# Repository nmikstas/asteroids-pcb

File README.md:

# asteroids-pcb
PCB source for the original Asteroids arcade game. This is a reproduction of a rev. 2 PCB. There are two sets of gerber files: the main Asteroids PCB and a small adapter board for IC 8C. 8C was a masked ROM that is no longer available. The adapter PCB will allow a 2716 EPROM to be used in it's place. A 28C16A-25 flash ROM will also work.

# NOTE
This project is part of my project portfolio: https://nmikstas.github.io/portfolio/

# Folder Structure
* Asteroids_PCB - The Kicad design files for the Asteroids PCB
* ROM_to_2716 - The Kicad source files for the ROM to EPROM adapter PCB
* Gerbers_Asteroids - The gerber files for the Asteroids PCB
* Gerbers_ROM_to_EPROM - The gerber files for the ROM to EPROM adapter PCB
* BOM - Bill of materials for the Asteroids PCB

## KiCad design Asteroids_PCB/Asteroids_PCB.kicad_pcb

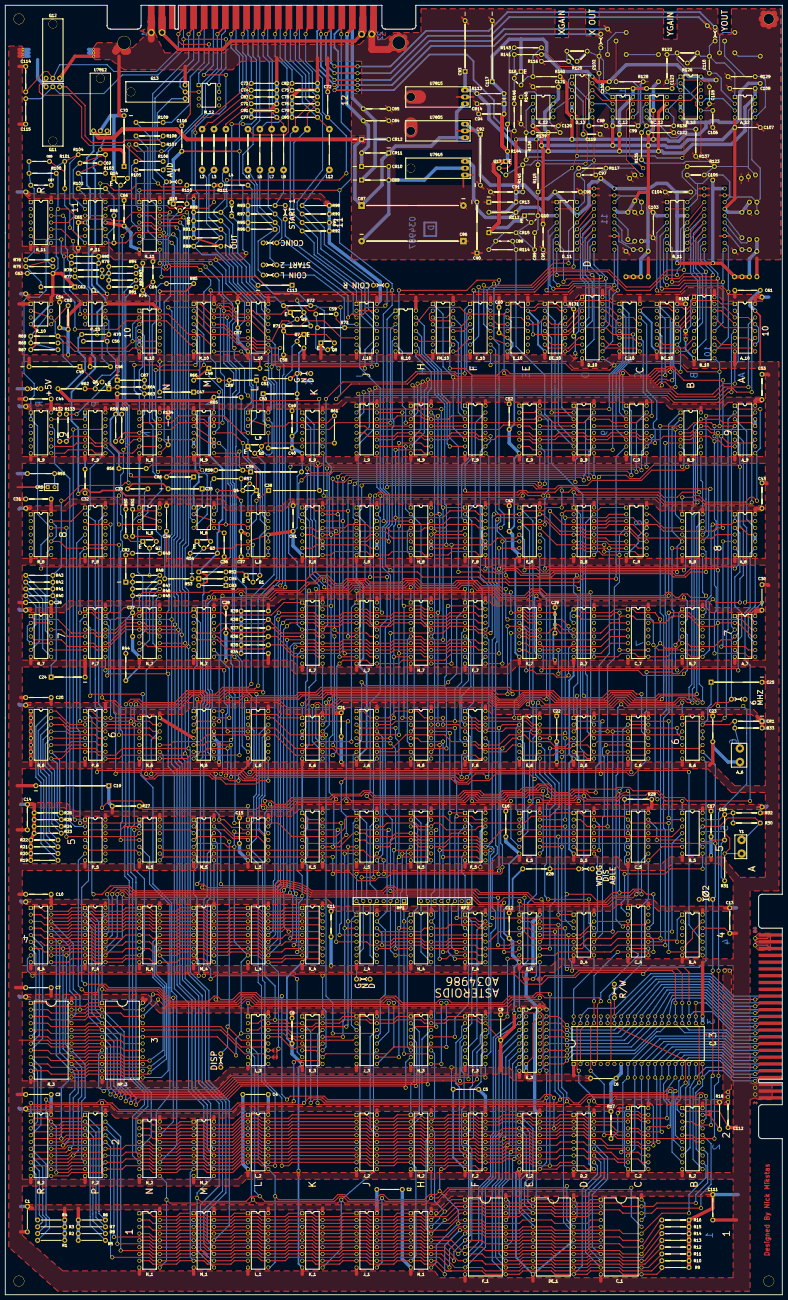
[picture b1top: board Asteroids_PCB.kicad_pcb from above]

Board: 2 copper layers, 290.8 x 482.6 mm, 490 parts (1 on the bottom side), 557 nets.

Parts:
A_6: RESET; RST
A_7: LS74; DIP14
A_8: LS10; DIP14
A_9: LS109; DIP16
A_10: LS157; DIP16
A_12: 082; DIP8
BC_10: LS157; DIP16
BC_12: 081; DIP8
B_2: LS244; DIP20
B_4: LS393; DIP14
B_5: LS04; DIP14
B_6: LS14; DIP14
B_7: LS161; DIP16
B_8: LS08; DIP14
B_9: LS32; DIP14
B_10: LS374; DIP20
B_11: AD561J; DIP16
B_11A1: ALT_DAC
B_12: 4016B; DIP14
C1, C2, C3, C4, C5, C6, C7, C8, C9, C10, C11, C12, C13, C14, C15, C16, C17, C18, C20, C21, C22, C23, C26, C28, C29, C30, C31, C34, C41, C42, C43, C44, C49, C52, C53, C57, C60, C61, C65, C66, C71, C72, C73, C74, C75, C76, C77, C78, C79, C80, C81, C82, C83, C84, C85, C91, C94, C111, C112: .1uF; GenericC
C19: 100uF; Electrolytic1
C24, C35, C47, C50, C62: 1uf; TantC
C25, C70, C90, C92, C93: 1uF; Electrolytic2C
C27, C32: .01uF; DiskC
C33: .22uF; Mylar_C
C36, C40, C55, C58: .01uf; DiskC
C37, C51, C54, C63, C95, C96, C99, C100, C103, C104, C107, C108, C114, C115, C116, C120, C121, C122, C123: .1uf; GenericC
C38, C39, C45, C48: 10uf; TantC2
C46: .047uf; Mylar_C
C56: .001uf; DiskC
C59: 270pf; Mylar_C
C64: .1uF; Mylar_C
C67, C68, C69: .1uf; Mylar_C
C86, C87: 470uF; Electrolytic3
C88: 390pf; SmallC
C89: 100pf; SmallC
C97, C105: 10pf; SmallC
C98, C106, C118, C119: 220pf; SmallC
C102, C110: 68pf; SmallC
C113: 1uF; TantC
C117: 22uF; Electrolytic4
CR1, CR2, CR3, CR4, CR6, CR7, CR8: 1N914; Diode1
CR5: LED
CR9, CR10, CR11, CR12: 1N4001; GenericD
CR13, CR14: 1N756A; GenericR
CR15: 1N914; GenericR
C_1: 8316E; DDIP24
C_2: LS244; DIP20
C_3: 6502A
C_4: 9316; DIP16
C_5, C_7: LS161; DIP16
C_6: LS00; DIP14
C_8: S287N; DIP16
C_9: LS191_; DIP16
C_10: LS157; DIP16
C_12: 082; DIP8
DE_1: 8316E; DDIP24
DE_10: LS157; DIP16
D_2: 2114; DIP18
D_4: LS74; DIP14
D_5: LS393; DIP14
D_6: LS02; DIP14
D_7: LS161; DIP16
D_8: LS174_; DIP16
D_9: LS191_; DIP16
D_10: LS374; DIP20
D_11: AD561J; DIP16
D_11A1: ALT_DAC
D_12: 4016B; DIP14
E_2: 2114; DIP18
E_3: LS245; DIP20
E_4: LS139; DIP16
E_5: LS20; DIP14
E_6: LS08; DIP14
E_7, E_8: LS42; DIP16
E_9: LS191_; DIP16
E_10: LS157; DIP16
E_12: 081; DIP8
FH_10: LS157; DIP16
F_1: 8316E; DDIP24
F_2: 82S137
F_3: LS157; DIP16
F_4: LS670; DIP16
F_5: LS193; DIP16
F_6: LS157_; DIP16
F_7: LS273; DIP20
F_8: SN5497; DIP16
F_9: LS191_; DIP16
F_10: LS174_; DIP16
H_1, H_2: 82S137
H_3: LS157; DIP16
H_4: LS670; DIP16
H_5: LS193; DIP16
H_6: LS367; DIP16
H_7: LS273; DIP20
H_8: SN5497; DIP16
H_9: LS191_; DIP16
H_10: LS04; DIP14
J20: J20
J21: J21
J_1, J_2: 82S137
J_3: LS157; DIP16
J_4: LS670; DIP16
J_5: LS193; DIP16
J_6: LS367; DIP16
J_7: LS273; DIP20
J_8: SN5497; DIP16
J_9: LS191_; DIP16
J_10: LS251; DIP16
K_1: 82S137
K_3: LS157; DIP16
K_4: 835185; DIP18
K_5: LS191; DIP16
K_6: LS08; DIP14
K_7: LS273; DIP20
K_8: SN5497; DIP16
K_9: LS164; DIP14
L2, L3, L4, L5, L6, L7, L8, L12: 100uH; GenericL
L_1, L_2: 82S137
L_3: LS139; DIP16
L_4: 835185; DIP18
L_5: LS04; DIP14
L_6: LS42; DIP16
L_8: 324; DIP14
L_9: 555; DIP8
L_10: LS251; DIP16
M_1, M_2: 82S137
M_4: 2114; DIP18
M_5: LS32; DIP14
M_6: LS83; DIP16
M_7: LS175; DIP16
M_8: 555; DIP8
M_9: 4016B; DIP14
M_10: LS259; DIP16
M_12: SW_DIP_x04; DIP8
NP_3: 8316E; DDIP24
N_1, N_2: 82S137
N_4: 2114; DIP18
N_5: LS00; DIP14
N_6: LS32; DIP14
N_7, N_11: LS174_; DIP16
N_8: 555; DIP8
N_9: LS06; DIP14
N_10: 4016B; DIP14
PD1, PD2, PD3, PD4, PD10, PD11, PD30, PD31: Split_Pad; SP
P_2: DIP20_DUMMY; DIP20
P_4: 2114; DIP18
P_5: LS86; DIP14
P_6: LS253; DIP16
P_7: LS174_; DIP16
P_8: LS161; DIP16
P_9: LS164; DIP14
P_10: 566; DIP8
P_11: 324; DIP14
Q1, Q2, Q3, Q4, Q5, Q7, Q10, Q16, Q17: 2N3906; GenericQ
Q6: 2N3643; GenericQ
Q8, Q9: 2N3904; GenericQ
Q11, Q12, Q13: 2N6044
Q14, Q15: MPSA06S; GenericQ
R1, R2, R3, R4, R5, R6, R7, R8, R45, R50: 22K; GenericR
R9, R10, R11, R12, R13, R14, R15, R16, R17, R18, R28, R33, R69, R110, R111, R130, R131: 10K; GenericR
R19, R20, R21, R22, R23, R24, R25, R26, R32, R87, R88, R89, R90, R91, R92, R93, R94, R95, R96, R97, R98, R99: 470; GenericR
R27, R29, R86: 1K; GenericR
R30, R31, R115: 330; GenericR
R34, R41: 22k; GenericR
R35, R100: 1.2k; GenericR
R36, R75, R117, R123, R133: 2.2k; GenericR
R37, R137, R140, R144: 4.7k; GenericR
R38, R54, R58, R59, R60, R63, R70, R79, R80, R103, R116, R122, R135, R136, R138, R139: 10k; GenericR
R39, R64, R106, R107, R108: 3.9k; GenericR
R40, R62, R67: 5.6k; GenericR
R42, R76, R114: 47k; GenericR
R43: 12k; GenericR
R44, R48, R78, R83: 47K; GenericR
R46, R81, R84, R143: 100K; GenericR
R47: 220K; GenericR
R49: 6.8K; GenericR
R51, R146: 18K; GenericR
R52: 33k; GenericR
R53, R73, R85, R132, R134: 1k; GenericR
R55: 150; GenericR
R56, R65: 3.3k; GenericR
R57, R61: 680; GenericR
R66: 2.7k; GenericC
R68: 15k; GenericR
R71: 68; GenericR
R72: 27; GenericR
R74, R142: 3.3K; GenericR
R77: 39K; GenericR
R82, R102: 4.7K; GenericR
R101: 270k; GenericR
R104, R128, R129: 6.8k; GenericR
R105, R109: 120; GenericR
R112, R113: 270; GenericR
R120, R126: 10k; Pot
R141: 2.2K; GenericR
R145: 56K; GenericR
RP1, RP2: R_Network07_10K; SIP8
R_2: LS245; DIP20
R_3: 8316E; DDIP24
R_4: 2114; DIP18
R_6: SW_x08; DIP16
R_7: LS08; DIP14
R_8: LS74; DIP14
R_9: LS164; DIP14
R_10: 555; DIP8
R_11: 4016B; DIP14
T1: TPAD1; TPAD
T2: TPAD2; TPAD
T3: TPAD3; TPAD
T4: TPAD4; TPAD
T5: TPAD5; TPAD
T6: TPAD6; TPAD
T7: TPAD7; TPAD
T10, T11, T12, T13, T14, T15, T16, T17: TPAD
TP1: WDOG_DISABLE; TEST_POINT
TP2: O2; TEST_POINT
TP3: R/W; TEST_POINT
TP4: 6MHz; TEST_POINT
TP5: +5V; TEST_POINT
TP6, TP7: GND; TEST_POINT
TP10: START 2; TEST_POINT
TP11: START 1; TEST_POINT
TP12: COIN R; TEST_POINT
TP13: COIN C; TEST_POINT
TP14: COIN L; TEST_POINT
TP20: AUD 1; TEST_POINT
TP30: DISP; TEST_POINT
TP50: X_OUT; TEST_POINT
TP60: Y_OUT; TEST_POINT
TP70: Z_OUT; TEST_POINT
U7805: L7805; Volt_Reg
U7812: L7812; 2N6044
U7815: L7815; Volt_Reg
U7915: L7915; Volt_Reg
Y1: 12.096MHz; RST

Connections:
1.5MHz: B_2.15, C_3.37, C_4.12
3KHz: B_4.8, C_5.2, D_5.1, L_10.3, R_11.11
3MHz: C_4.13, C_6.2, C_6.13, D_4.3, E_5.12, K_9.8
6MHz: A_7.3, A_9.4, B_10.11, C_4.14, D_10.11, F_10.9, TP4.1, TP4.2
12KHz: B_4.10, D_6.2, P_8.2, P_9.8, R_9.8
22V0: C37.1, C65.2, C87.1, CR11.1, CR12.1, L_8.4, P_11.4, U7805.1, U7812.1, U7815.1
36VAC1_: C84.1, CR10.1, CR11.2, J20.X
36_VAC2_: C85.1, CR9.1, CR12.2, J20.20
+5DAC: B_11.14, B_11A1.20, C92.1, C96.2, C104.2, D_11.14, D_11A1.20, U7805.3
+5V: A_7.14, A_8.14, A_9.16, A_10.16, BC_10.16, B_2.20, B_4.14, B_5.14, B_6.14, B_7.16, B_8.14, B_9.14, B_10.20, C1.1, C2.1, C3.1, C4.1, C5.1, C6.1, C7.1, C8.1, C9.1, C10.1, C11.1, C12.1, C13.1, C14.1, C15.1, C16.1, C17.1, C19.1, C20.1, C21.1, C22.1, C23.1, C26.1, C28.1, C29.1, C30.1, C31.1, C34.1, C41.1, C42.1, C43.1, C44.1, C49.1, C51.1, C52.1, C53.1, C54.1, C57.1, C60.1, C61.1, C62.1, C63.2, C66.1, C111.1, C112.1, CR1.1, C_1.21, C_1.24, C_2.20, C_3.8, C_4.16, C_5.16, C_6.14, C_7.16, C_8.16, C_9.16, C_10.16, DE_1.21, DE_1.24, DE_10.16, D_2.18, D_4.14, D_5.14, D_6.14, D_7.16, D_8.16, D_9.16, D_10.20, E_2.18, E_3.20, E_4.16, E_5.14, E_6.14, E_7.16, E_8.16, E_9.16, E_10.16, FH_10.16, F_1.21, F_1.24, F_2.18, F_3.16, F_4.16, F_5.16, F_6.16, F_7.20, F_8.16, F_9.16, F_10.16, H_1.18, H_2.18, H_3.16, H_4.16, H_5.16, H_6.16, H_7.20, H_8.16, H_9.16, H_10.14, J20.2, J20.21, J20.B, J20.Y, J21.45, J21.46, J21.47, J21.48, J21.49, J21.50, J_1.18, J_2.18, J_3.16, J_4.16, J_5.16, J_6.16, J_7.20, J_8.16, J_9.16, J_10.16, K_1.18, K_3.16, K_4.18, K_5.16, K_6.14, K_7.20, K_8.16, K_9.14, L_1.18, L_2.18, L_3.16, L_4.18, L_5.14, L_6.16, L_9.8, L_10.16, M_1.18, M_2.18, M_4.18, M_5.14, M_6.5, M_7.16, M_8.8, M_9.1, M_9.3, M_9.9, M_9.10, M_10.16, NP_3.21, NP_3.24, N_1.18, N_2.18, N_4.18, N_5.14, N_6.14, N_7.16, N_8.8, N_9.14, N_11.16, P_2.20, P_4.18, P_5.14, P_6.16, P_7.16, P_8.16, P_9.14, P_11.3, P_11.5, P_11.10, P_11.12, Q9.3, R1.1, R2.1, R3.1, R4.1, R5.2, R6.2, R7.2, R8.2, R9.2, R10.2, R11.1, R12.2, R13.1, R14.2, R15.1, R16.1, R17.1, R18.1, R19.1, R20.1, R21.1, R22.1, R23.1, R24.1, R25.1, R26.1, R27.2, R28.1, R29.2, R33.1, R39.1, R49.1, R50.1, R55.1, R67.1, R71.1, R79.1, R80.1, R87.2, R88.2, R89.2, R90.2, R91.2, R92.2, R93.2, R94.2, R95.2, R96.2, R97.2, R98.2, R99.2, R100.1, R130.2, R131.2, R132.2, R134.1, RP1.1, RP2.1, R_2.20, R_3.21, R_3.24, R_4.18, R_7.14, R_8.14, R_9.14, R_10.4, R_10.8, R_11.14, TP5.1, TP5.2
+8.2V: B_12.14, C94.1, C117.1, CR14.1, CR15.1, D_12.14, Q10.1, Q16.1, Q17.1, R113.1, R141.1, R144.1
+12V: C70.1, CR3.2, M_9.14, N_10.14, P_10.8, R52.1, R54.1, R56.1, R59.1, R60.1, R62.1, R63.1, R65.1, R70.1, R85.1, U7812.3
+15V: A_12.8, BC_12.7, C93.1, C100.2, C108.2, C121.2, C123.2, C_12.8, E_12.7, R113.2, U7815.3
-8.2V: B_12.7, C91.1, CR13.2, D_12.7, R112.1, R115.2, R142.2, R145.2
-15V: A_12.4, BC_12.4, B_11.3, B_11A1.17, C90.1, C95.1, C99.2, C103.1, C107.2, C120.2, C122.2, C_12.4, D_11.3, D_11A1.17, E_12.4, R112.2, U7915.3
A0: C_2.13, C_3.9, J21.17
A1: C_2.8, C_3.10, J21.18
A2: C_2.11, C_3.11, J21.15
A3: C_2.6, C_3.12, J21.16
A4: C_2.15, C_3.13, J21.13
A5: C_2.4, C_3.14, J21.14
A6: C_2.2, C_3.15, J21.11
A7: C_2.17, C_3.16, J21.12
A8: B_2.6, C_3.17, J21.9
A9: B_2.4, C_3.18, J21.10
A10: B_2.8, C_3.19, J21.7
A11: B_2.13, C_3.20, J21.8
A12: B_2.11, C_3.22, J21.21
A13: C_3.23, E_4.14, J21.22
A14: C_3.24, E_4.13, J21.19
A15: C_3.25, J21.20, PD1.1
AB0: C_1.8, C_2.7, DE_1.8, D_2.5, E_2.5, F_1.8, F_2.5, F_3.11, H_1.5, H_2.5, J_1.5, J_2.5, J_10.11, K_1.5, L_1.5, L_2.5, L_10.11, M_1.5, M_2.5, M_10.1, N_1.5, N_2.5, P_6.14
AB1: C_1.7, C_2.12, DE_1.7, D_2.6, E_2.6, F_1.7, F_2.6, F_3.5, H_1.6, H_2.6, J_1.6, J_2.6, J_10.10, K_1.6, L_1.6, L_2.6, L_10.10, M_1.6, M_2.6, M_10.2, N_1.6, N_2.6, P_6.2
AB2: C_1.6, C_2.9, DE_1.6, D_2.7, E_2.7, F_1.6, F_2.7, F_3.2, H_1.7, H_2.7, J_1.7, J_2.7, J_10.9, K_1.7, L_1.7, L_2.7, L_10.9, M_1.7, M_2.7, M_10.3, N_1.7, N_2.7
AB3: C_1.5, C_2.14, DE_1.5, D_2.4, E_2.4, F_1.5, F_2.4, F_3.14, H_1.4, H_2.4, J_1.4, J_2.4, K_1.4, L_1.4, L_2.4, M_1.4, M_2.4, N_1.4, N_2.4
AB4: C_1.4, C_2.5, DE_1.4, D_2.3, E_2.3, F_1.4, F_2.3, H_1.3, H_2.3, H_3.14, J_1.3, J_2.3, K_1.3, L_1.3, L_2.3, M_1.3, M_2.3, N_1.3, N_2.3
AB5: C_1.3, C_2.16, DE_1.3, D_2.2, E_2.2, F_1.3, F_2.2, H_1.2, H_2.2, H_3.2, J_1.2, J_2.2, K_1.2, L_1.2, L_2.2, M_1.2, M_2.2, N_1.2, N_2.2
AB6: C_1.2, C_2.18, DE_1.2, D_2.1, E_2.1, F_1.2, F_2.1, H_1.1, H_2.1, H_3.5, J_1.1, J_2.1, K_1.1, L_1.1, L_2.1, M_1.1, M_2.1, N_1.1, N_2.1
AB7: C_1.1, C_2.3, DE_1.1, D_2.17, E_2.17, F_1.1, F_2.17, H_1.17, H_2.17, H_3.11, J_1.17, J_2.17, K_1.17, L_1.17, L_2.17, M_1.17, M_2.17, N_1.17, N_2.17
AB8: B_2.14, C_1.23, DE_1.23, F_1.23, F_2.16, H_1.16, H_2.16, J_1.16, J_2.16, J_3.11, K_1.16, L_1.16, L_2.16, M_1.16, M_2.16, N_1.16, N_2.16, P_5.4
AB9: B_2.16, C_1.22, DE_1.22, D_2.15, E_2.15, F_1.22, F_2.15, H_1.15, H_2.15, J_1.15, J_2.15, J_3.14, K_1.15, L_1.15, L_2.15, L_6.15, M_1.15, M_2.15, N_1.15, N_2.15, N_5.5
AB10: B_2.12, C_1.19, DE_1.19, E_4.2, F_1.19, F_2.8, H_1.8, H_2.8, J_1.8, J_2.8, J_3.2, K_1.8, L_5.5, L_6.14
AB11: B_2.7, E_4.3, K_3.2, L_3.2, L_6.13
AB12: B_2.9, D_6.8, E_5.9, K_3.14, L_3.3
ADMA0: C_8.5, D_8.12, E_8.15, F_3.10
ADMA1: F_3.6, F_4.15, F_5.3
ADMA2: F_3.3, F_4.1, F_5.2
ADMA3: F_3.13, F_4.2, F_5.6
ADMA4: F_4.3, F_5.7, H_3.13
ADMA5: H_3.3, H_4.15, H_5.3
ADMA6: H_3.6, H_4.1, H_5.2
ADMA7: H_3.10, H_4.2, H_5.6
ADMA8: H_4.3, H_5.7, J_3.10
ADMA9: J_3.13, J_4.15, J_5.3
ADMA10: J_3.3, J_4.1, J_5.2
ADMA11: J_4.2, J_5.6, K_3.3
ADMA12: J_4.3, J_5.7, K_3.13
AM0: F_3.9, K_4.5, L_4.5, M_4.5, NP_3.8, N_4.5, P_4.5, R_3.8, R_4.5
AM1: F_3.7, K_4.6, L_4.6, M_4.6, NP_3.7, N_4.6, P_4.6, R_3.7, R_4.6
AM2: F_3.4, K_4.7, L_4.7, M_4.7, NP_3.6, N_4.7, P_4.7, R_3.6, R_4.7
AM3: F_3.12, K_4.4, L_4.4, M_4.4, NP_3.5, N_4.4, P_4.4, R_3.5, R_4.4
AM4: H_3.12, K_4.3, L_4.3, M_4.3, NP_3.4, N_4.3, P_4.3, R_3.4, R_4.3
AM5: H_3.4, K_4.2, L_4.2, M_4.2, NP_3.3, N_4.2, P_4.2, R_3.3, R_4.2
AM6: H_3.7, K_4.1, L_4.1, M_4.1, NP_3.2, N_4.1, P_4.1, R_3.2, R_4.1
AM7: H_3.9, K_4.17, L_4.17, M_4.17, NP_3.1, N_4.17, P_4.17, R_3.1, R_4.17
AM8: J_3.9, K_4.16, L_4.16, M_4.16, NP_3.23, N_4.16, P_4.16, R_3.23, R_4.16
AM9: J_3.12, K_4.15, L_4.15, M_4.15, NP_3.22, N_4.15, P_4.15, R_3.22, R_4.15
AM10: J_3.4, K_4.8, L_4.8, L_5.3, M_5.5, NP_3.19, R_3.19
AM11: K_3.4, L_3.14
AM12: K_3.12, L_3.13
AUDIO_1_: C113.2, J20.5, P_11.8, R86.1, TP20.1, TP20.2
AUDIO_2_: J20.E, P_11.14, R110.1
BVLD: B_8.8, K_9.2
C1: C115.1, J20.4, M_12.7, M_12.8, Q11.2
C_CN_SW_: C81.2, J20.12, L7.1
D0: C_3.33, E_3.18, J21.29
D1: C_3.32, E_3.17, J21.30
D2: C_3.31, E_3.16, J21.27
D3: C_3.30, E_3.15, J21.28
D4: C_3.29, E_3.14, J21.25
D5: C_3.28, E_3.13, J21.26
D6: C_3.27, E_3.12, J21.23
D7: C_3.26, E_3.11, J21.24
DACX1: C_10.9, D_10.13
DACX1*: D_10.12, D_11.4, D_11A1.12
DACX2: C_10.7, D_10.14
DACX2*: D_10.15, D_11.5, D_11A1.11
DACX3: C_10.12, D_10.17
DACX3*: D_10.16, D_11.6, D_11A1.10
DACX4: C_10.4, D_10.18
DACX4*: D_10.19, D_11.7, D_11A1.9
DACX5: DE_10.9, D_10.8
DACX5*: D_10.9, D_11.8, D_11A1.8
DACX6: DE_10.7, D_10.7
DACX6*: D_10.6, D_11.9, D_11A1.7
DACX7: DE_10.12, D_10.4
DACX7*: D_10.5, D_11.10, D_11A1.6
DACX8: DE_10.4, D_10.3
DACX8*: D_10.2, D_11.11, D_11A1.5
DACX9: E_10.12, F_10.13
DACX9*: D_11.12, D_11A1.4, F_10.12
DACX10: E_10.4, F_10.14
DACX10*: D_11.13, D_11A1.3, F_10.15
DACY1: A_10.9, B_10.13
DACY1*: B_10.12, B_11.4, B_11A1.12
DACY2: A_10.7, B_10.14
DACY2*: B_10.15, B_11.5, B_11A1.11
DACY3: A_10.12, B_10.17
DACY3*: B_10.16, B_11.6, B_11A1.10
DACY4: A_10.4, B_10.18
DACY4*: B_10.19, B_11.7, B_11A1.9
DACY5: BC_10.9, B_10.8
DACY5*: B_10.9, B_11.8, B_11A1.8
DACY6: BC_10.7, B_10.7
DACY6*: B_10.6, B_11.9, B_11A1.7
DACY7: BC_10.12, B_10.4
DACY7*: B_10.5, B_11.10, B_11A1.6
DACY8: BC_10.4, B_10.3
DACY8*: B_10.2, B_11.11, B_11A1.5
DACY9: FH_10.9, F_10.6
DACY9*: B_11.12, B_11A1.4, F_10.7
DACY10: FH_10.12, F_10.4
DACY10*: B_11.13, B_11A1.3, F_10.5
DB0: C_1.9, DE_1.9, D_2.14, E_3.2, F_1.9, H_1.14, J_1.14, K_1.14, L_1.14, M_1.14, N_1.14, N_7.6, N_11.14, P_2.17, P_6.7, R14.1, R_2.16
DB1: C_1.10, DE_1.10, D_2.13, E_3.3, F_1.10, H_1.13, J_1.13, K_1.13, L_1.13, M_1.13, N_1.13, N_7.11, N_11.3, P_2.18, P_6.9, R12.1, R_2.17
DB2: C_1.11, DE_1.11, D_2.12, E_3.4, F_1.11, H_1.12, J_1.12, K_1.12, L_1.12, M_1.12, N_1.12, N_7.4, N_11.13, P_2.19, P_7.6, R10.1, R_2.18
DB3: C_1.13, DE_1.13, D_2.11, E_3.5, F_1.13, H_1.11, J_1.11, K_1.11, L_1.11, M_1.11, N_1.11, N_7.13, N_11.4, P_2.16, P_7.11, R9.1, R_2.15
DB4: C_1.14, DE_1.14, E_2.14, E_3.6, F_1.14, F_2.14, H_2.14, J_2.14, L_2.14, M_2.14, N_2.14, N_7.3, N_11.11, P_2.15, P_7.4, R11.2, R_2.14
DB5: C_1.15, DE_1.15, E_2.13, E_3.7, F_1.15, F_2.13, H_2.13, J_2.13, L_2.13, M_2.13, N_2.13, N_11.6, P_2.14, P_7.13, R13.2, R_2.13
DB6: C_1.16, DE_1.16, E_2.12, E_3.8, F_1.16, F_2.12, H_2.12, J_2.12, L_2.12, M_2.12, N_2.12, P_2.13, P_7.3, R15.2, R_2.12
DB7: C_1.17, DE_1.17, E_2.11, E_3.9, F_1.17, F_2.11, H_2.11, J_2.11, J_10.6, L_2.11, L_10.6, M_2.11, M_10.13, N_2.11, P_2.12, P_7.14, R16.2, R_2.11
DDMA0: F_7.18, H_7.18, J_7.18, K_7.18, L_4.14, M_4.14, NP_3.9, N_4.14, P_2.3, R8.1, R_2.4, R_3.9
DDMA1: F_7.3, H_7.3, J_7.3, K_7.3, L_4.13, M_4.13, NP_3.10, N_4.13, P_2.2, R7.1, R_2.3, R_3.10
DDMA2: F_7.17, H_7.17, J_7.17, K_7.17, L_4.12, M_4.12, NP_3.11, N_4.12, P_2.1, R6.1, R_2.2, R_3.11
DDMA3: F_7.4, H_7.4, J_7.4, K_7.4, L_4.11, M_4.11, NP_3.13, N_4.11, P_2.4, R5.1, R_2.5, R_3.13
DDMA4: F_7.14, H_7.14, J_7.14, K_4.14, K_7.14, NP_3.14, P_2.5, P_4.14, R1.2, R_2.6, R_3.14, R_4.14
DDMA5: F_7.7, H_7.7, J_7.7, K_4.13, K_7.7, NP_3.15, P_2.6, P_4.13, R2.2, R_2.7, R_3.15, R_4.13
DDMA6: F_7.13, H_7.13, J_7.13, K_4.12, K_7.13, NP_3.16, P_2.7, P_4.12, R3.2, R_2.8, R_3.16, R_4.12
DDMA7: F_7.8, H_7.8, J_7.8, K_4.11, K_7.8, NP_3.17, P_2.8, P_4.11, R4.2, R_2.9, R_3.17, R_4.11
DIAG_STEP_: C71.2, J20.K, L4.1
DVX0: E_9.15, J_7.19, J_8.14
DVX1: E_9.1, J_7.2, J_8.15
DVX2: E_9.10, J_7.16, J_8.2
DVX3: E_9.9, J_7.5, J_8.3
DVX4: D_9.15, J_7.15, K_8.4
DVX5: D_9.1, J_7.6, K_8.1
DVX6: D_9.10, J_7.12, K_8.14
DVX7: D_9.9, J_7.9, K_8.15
DVX8: C_9.15, K_7.19, K_8.2
DVX9: C_9.1, K_7.2, K_8.3
DVX10: C_9.5, C_9.10, D_9.5, E_9.5, K_7.16
DVX11: B_6.3, C_9.9, F_6.11, K_7.5
DVY0: H_6.2, H_7.19, H_8.14, J_9.15
DVY1: H_6.14, H_7.2, H_8.15, J_9.1
DVY2: H_6.12, H_7.16, H_8.2, J_9.10
DVY3: H_6.4, H_7.5, H_8.3, J_9.9
DVY4: F_8.4, H_6.10, H_7.15, H_9.15
DVY5: F_8.1, H_6.6, H_7.6, H_9.1
DVY6: F_8.14, H_7.12, H_9.10, J_6.4
DVY7: F_8.15, H_7.9, H_9.9, J_6.2
DVY8: F_7.19, F_8.2, F_9.15, J_6.10
DVY9: F_7.2, F_8.3, F_9.1, J_6.6
DVY10: F_7.16, F_9.5, F_9.10, H_9.5, J_6.12, J_9.5
DVY11: F_6.14, F_7.5, F_9.9, J_6.14
EXPAUD0: P_7.12, R_7.1
EXPAUD1: P_7.5, R_7.12
EXPAUD2: P_7.10, R_7.4
EXPAUD3: P_7.7, R_7.9
EXPITCH0: L_5.11, N_6.12, P_7.2, P_8.4
EXPITCH1: N_6.13, P_7.15, P_8.3
EXPLOSND: C24.2, R40.1, R41.1, R42.1, R43.1, R82.2
FIRE_: C72.2, J20.T, L_10.15, R89.1
GND: A_6.1, A_7.7, A_8.7, A_9.8, A_10.8, A_10.15, BC_10.8, BC_10.15, B_2.1, B_2.10, B_2.19, B_4.2, B_4.7, B_4.12, B_5.7, B_6.7, B_7.8, B_8.7, B_9.7, B_10.1, B_10.10, B_11.1, B_11A1.1, B_11A1.2, B_11A1.13, B_11A1.19, C1.2, C2.2, C3.2, C4.2, C5.2, C6.2, C7.2, C8.2, C9.2, C10.2, C11.2, C12.2, C13.2, C14.2, C15.2, C16.2, C17.2, C19.2, C20.2, C21.2, C22.2, C23.2, C24.1, C25.2, C26.2, C27.2, C28.2, C29.2, C30.2, C31.2, C32.2, C33.2, C34.2, C35.2, C36.2, C37.2, C38.2, C39.1, C40.2, C41.2, C42.2, C43.2, C44.2, C45.2, C46.2, C47.2, C48.1, C49.2, C50.2, C51.2, C52.2, C53.2, C54.2, C55.2, C57.2, C58.2, C60.2, C61.2, C63.1, C64.2, C65.1, C66.2, C70.2, C71.1, C72.1, C73.1, C74.1, C75.1, C76.1, C77.1, C78.1, C79.1, C80.1, C81.1, C82.1, C83.1, C84.2, C85.2, C86.2, C87.2, C90.2, C91.2, C92.2, C93.2, C94.2, C95.2, C96.1, C98.2, C99.1, C100.1, C103.2, C104.1, C106.2, C107.1, C108.1, C111.2, C112.2, C114.2, C115.2, C116.2, C117.2, C118.2, C119.2, C120.1, C121.1, C122.1, C123.1, CR5.1, CR7.1, CR13.1, CR14.2, C_1.12, C_1.18, C_2.1, C_2.10, C_2.19, C_3.1, C_3.21, C_4.8, C_5.3, C_5.4, C_5.6, C_5.8, C_6.7, C_7.8, C_8.8, C_8.13, C_8.14, C_9.8, C_10.8, C_10.15, DE_1.12, DE_1.18, DE_10.8, DE_10.15, D_2.9, D_4.7, D_5.7, D_6.7, D_7.8, D_8.8, D_9.8, D_10.1, D_10.10, D_11.1, D_11A1.1, D_11A1.2, D_11A1.13, D_11A1.19, E_2.9, E_3.10, E_3.19, E_4.8, E_4.15, E_5.7, E_6.7, E_7.8, E_8.8, E_9.8, E_10.6, E_10.8, E_10.15, FH_10.3, FH_10.8, FH_10.15, F_1.12, F_1.18, F_2.9, F_3.8, F_3.15, F_4.8, F_5.8, F_5.14, F_6.5, F_6.8, F_6.15, F_7.10, F_8.8, F_9.8, F_10.8, H_1.9, H_2.9, H_3.8, H_3.15, H_4.8, H_5.8, H_5.14, H_6.8, H_7.10, H_8.1, H_8.4, H_8.8, H_9.8, H_10.7, J20.1, J20.11, J20.22, J20.A, J20.U, J20.V, J20.Z, J21.1, J21.2, J21.3, J21.4, J21.5, J21.6, J_1.9, J_2.9, J_3.8, J_3.15, J_4.8, J_5.8, J_5.14, J_6.8, J_7.10, J_8.1, J_8.4, J_8.8, J_9.8, J_10.8, K_1.9, K_3.8, K_3.15, K_4.9, K_5.1, K_5.4, K_5.8, K_5.9, K_5.10, K_5.15, K_6.7, K_7.10, K_8.8, K_9.7, L_1.9, L_2.9, L_3.8, L_3.15, L_4.9, L_5.7, L_6.8, L_8.5, L_8.10, L_8.11, L_9.1, L_10.8, M_1.9, M_2.9, M_4.9, M_5.7, M_6.12, M_6.13, M_7.8, M_8.1, M_9.7, M_10.8, NP_3.12, NP_3.18, N_1.9, N_2.9, N_4.9, N_5.7, N_6.7, N_7.8, N_8.1, N_9.7, N_10.1, N_10.3, N_10.7, N_11.8, PD1.2, PD2.1, PD2.2, PD3.1, PD3.2, PD4.1, PD4.2, PD30.1, PD30.2, PD31.1, PD31.2, P_2.10, P_4.9, P_5.7, P_6.8, P_7.8, P_8.8, P_9.7, P_10.1, P_11.11, Q7.3, Q8.1, Q11.3, Q12.3, Q13.3, Q14.1, Q15.1, R17.2, R18.2, R32.2, R34.2, R44.2, R53.2, R72.2, R116.2, R122.2, R128.2, R129.2, R130.1, R131.1, R137.2, R140.2, R_2.10, R_3.12, R_3.18, R_4.9, R_6.1, R_6.2, R_6.3, R_6.4, R_6.5, R_6.6, R_6.7, R_6.8, R_7.7, R_8.7, R_9.7, R_10.1, R_11.7, TP6.1, TP6.2, TP7.1, TP7.2, U7805.2, U7812.2, U7815.2, U7915.1
GO: A_9.6, B_7.9, C_7.9, D_7.7, D_7.9, D_7.10, H_10.1
GR: B_5.4, F_4.11, H_4.11, J_4.11
GW: C_6.3, F_4.12, H_4.12, J_4.12
HALT: A_9.10, D_8.14, L_10.2
HYPRSPC_: C73.2, J20.10, L_10.1, R88.1
INV: B_12.13, D_12.13, Q16.3, R142.1, R143.2
L1: C114.1, J20.D, M_12.1, Q12.2
LIFEEN: M_10.10, R79.2, R_11.12
LIFESND: R78.2, R_11.10
LOAD1: F_4.10, F_5.15, H_6.3, RP2.3
LOAD2: F_4.9, F_5.1, H_6.13, RP2.4
LOAD3: F_4.7, F_5.10, H_6.11, RP2.6
LOAD4: F_4.6, F_5.9, H_6.5, RP2.5
LOAD5: H_4.10, H_5.15, H_6.9, RP2.7
LOAD6: H_4.9, H_5.1, H_6.7, RP2.8
LOAD7: H_4.7, H_5.10, J_6.5, RP1.3
LOAD8: H_4.6, H_5.9, J_6.3, RP1.2
LOAD9: J_4.10, J_5.15, J_6.9, RP1.5
LOAD10: J_4.9, J_5.1, J_6.7, RP1.6
LOAD11: J_4.7, J_5.10, J_6.11, RP1.7
LOAD12: J_4.6, J_5.9, J_6.13, RP1.8
L_CN_SW_: C82.2, J20.13, L5.1
NINV: B_12.12, D_12.12, Q17.3, R145.1
NOISE: N_5.3, R_8.12, R_9.1, R_9.2, R_11.9
NO_CON: J20.19, R146.2
unnamed: A_6.2, B_6.13, C25.1, CR1.2, R33.2
unnamed: A_7.5, A_8.3, A_8.10, A_8.11
unnamed: A_7.8, B_9.5
unnamed: A_7.9, A_8.5
unnamed: A_7.10, A_8.8
unnamed: A_8.1, A_8.2, A_8.13, B_7.15
unnamed: A_8.4, C_8.4, D_6.12, D_8.7
unnamed: A_8.6, E_8.12
unnamed: A_8.9, L_5.12
unnamed: A_9.2, B_6.2
unnamed: A_9.15, B_8.11
unnamed: A_12.2, C110.1, R122.1, R126.3
unnamed: A_12.3, B_12.2, B_12.10
unnamed: A_12.5, R129.1
unnamed: A_12.7, B_12.8, C105.1, R123.1, R135.2
unnamed: BC_12.2, R135.1, R136.2
unnamed: BC_12.3, R137.1
unnamed: BC_12.6, B_12.4, R136.1
unnamed: B_4.1, C_4.11
unnamed: B_4.6, B_4.13
unnamed: B_5.2, C_6.1
unnamed: B_5.5, C_5.15
unnamed: B_5.6, C_3.6, C_5.9
unnamed: B_5.8, C_4.2
unnamed: B_5.10, C18.1, R31.1
unnamed: B_5.11, R31.2, Y1.2
unnamed: B_5.9, B_5.12, R30.2, Y1.1
unnamed: B_5.13, C18.2, R30.1, R32.1
unnamed: B_6.4, F_6.2
unnamed: B_6.10, C_6.5, D_4.10
unnamed: B_6.11, B_6.12
unnamed: B_7.3, E_7.9
unnamed: B_7.4, E_7.10
unnamed: B_7.5, E_7.11
unnamed: B_7.7, B_7.10, C_7.15
unnamed: B_8.3, C_8.15
unnamed: B_8.6, F_5.5
unnamed: B_9.3, K_6.12
unnamed: B_9.6, D_8.9
unnamed: B_9.8, K_6.9
unnamed: B_9.10, D_4.6
unnamed: B_11.16, R123.2
unnamed: B_11A1.14, T7.1
unnamed: B_11A1.15, T6.1
unnamed: B_11A1.16, T5.1
unnamed: B_12.1, B_12.3, C118.1
unnamed: B_12.9, B_12.11, C106.1
unnamed: C27.1, CR2.1, Q2.2, R44.1, R45.1, R46.1, R47.1, R48.1
unnamed: C32.1, N_8.5
unnamed: C33.1, N_8.2, N_8.6, Q2.3, R51.2
unnamed: C35.1, M_8.2, M_8.6, R57.2
unnamed: C36.1, M_8.5
unnamed: C38.1, L_8.3, M_9.4, Q3.3
unnamed: C39.2, M_9.8, R58.1
unnamed: C40.1, L_9.5
unnamed: C45.1, N_10.2, N_10.9, Q6.2, R69.2, R_10.2, R_10.6
unnamed: C46.1, P_10.7
unnamed: C47.1, L_8.12, M_9.11, Q1.3
unnamed: C48.2, M_9.2, R66.1
unnamed: C50.1, L_9.2, L_9.6, R61.2
unnamed: C55.1, R_10.5
unnamed: C56.1, P_10.6, R70.2
unnamed: C56.2, P_10.5, Q6.3, R62.2
unnamed: C58.1, Q7.1, Q8.3, Q9.2, R71.2
unnamed: C59.1, Q8.2, R73.1
unnamed: C59.2, H_10.4, R73.2
unnamed: C62.2, R75.1, R76.2
unnamed: C64.1, N_8.3, R74.1
unnamed: C67.1, P_11.7, R101.1, R104.2
unnamed: C67.2, C68.1, R76.1, R100.2
unnamed: C68.2, P_11.6, R101.2
unnamed: C69.2, P_11.2, R103.2, R104.1
unnamed: C86.1, CR9.2, CR10.2, U7915.2
unnamed: C88.1, C89.1, CR15.2, Q10.2, R114.1
unnamed: C88.2, C_6.11, R114.2
unnamed: C97.1, C_12.7, D_12.8, R117.1, R138.2
unnamed: C97.2, C_12.6, D_11.2, D_11.15
unnamed: C98.1, D_12.9, D_12.11
unnamed: C102.1, C_12.2, R116.1, R120.3
unnamed: C113.1, R111.2
unnamed: C119.1, D_12.1, D_12.3
unnamed: CR2.2, R49.2
unnamed: CR3.1, CR4.2
unnamed: CR4.1, Q1.2, Q3.2, R53.1
unnamed: CR5.2, R55.2
unnamed: CR6.1, M_8.3
unnamed: CR7.2, N_10.4, R64.1
unnamed: CR8.1, L_9.3
unnamed: C_6.6, D_5.2, D_5.12
unnamed: C_6.8, E_4.1
unnamed: C_6.10, D_6.10
unnamed: C_7.3, E_7.4
unnamed: C_7.4, E_7.5
unnamed: C_7.5, E_7.6
unnamed: C_7.6, E_7.7
unnamed: C_7.7, C_7.10, D_7.15
unnamed: C_8.1, E_6.6
unnamed: C_8.2, E_6.3
unnamed: C_8.3, E_6.11
unnamed: C_8.6, D_8.5, E_8.14
unnamed: C_8.7, D_8.10, E_8.13, L_5.13
unnamed: C_8.9, D_8.6
unnamed: C_8.10, D_8.11
unnamed: C_8.11, D_8.4
unnamed: C_8.12, D_8.13
unnamed: C_9.4, D_9.13
unnamed: C_9.7, H_10.13
unnamed: C_9.14, D_9.14, E_9.14, H_10.6
unnamed: C_12.3, D_12.2, D_12.10
unnamed: C_12.5, R128.1
unnamed: D_2.8, E_2.8, M_5.11
unnamed: D_2.16, E_2.16, P_5.6
unnamed: D_4.11, D_5.8
unnamed: D_4.12, E_6.8
unnamed: D_5.6, D_5.13
unnamed: D_6.1, R_8.11
unnamed: D_6.3, L_5.2, P_8.9
unnamed: D_6.4, E_5.13
unnamed: D_6.5, D_6.9, E_4.11
unnamed: D_6.11, D_8.15
unnamed: D_7.4, E_7.1
unnamed: D_7.5, E_7.2
unnamed: D_7.6, E_7.3
unnamed: D_9.4, E_9.13
unnamed: D_11.16, R117.2
unnamed: D_11A1.14, T4.1
unnamed: D_11A1.15, T3.1
unnamed: D_11A1.16, T2.1
unnamed: D_11A1.18, T1.1
unnamed: D_12.4, E_12.6, R139.1
unnamed: E_5.8, L_6.12
unnamed: E_6.10, R28.2, TP1.1, TP1.2
unnamed: E_7.12, M_6.15
unnamed: E_7.13, M_6.2
unnamed: E_7.14, M_6.6
unnamed: E_7.15, M_6.9
unnamed: E_12.2, R138.1, R139.2
unnamed: E_12.3, R140.1
unnamed: F_5.12, H_5.5
unnamed: F_6.4, M_6.7
unnamed: F_6.7, M_6.16
unnamed: F_6.9, M_6.4
unnamed: F_6.12, M_6.11
unnamed: F_7.1, K_6.3, K_6.4
unnamed: F_8.5, H_8.12
unnamed: F_8.7, H_8.10, H_8.11
unnamed: F_9.4, H_9.13
unnamed: F_9.7, H_10.11
unnamed: F_9.14, H_9.14, H_10.8, J_9.14
unnamed: H_5.12, J_5.5
unnamed: H_7.1, K_6.6
unnamed: H_9.4, J_9.13
unnamed: H_10.3, K_9.3
unnamed: H_10.5, J_8.6
unnamed: H_8.6, H_10.9
unnamed: J_8.10, J_8.11, K_8.7
unnamed: J_8.12, K_8.5
unnamed: J_10.1, L8.2, R93.1, TP11.1, TP11.2
unnamed: J_10.2, L12.2, R98.1, TP12.1, TP12.2
unnamed: J_10.3, L7.2, R97.1, TP13.1, TP13.2
unnamed: J_10.4, L5.2, R96.1, TP14.1, TP14.2
unnamed: J_10.15, L6.2, R95.1, TP10.1, TP10.2
unnamed: K_3.7, M_5.9
unnamed: K_5.14, K_6.8
unnamed: K_6.11, K_7.11
unnamed: L3.2, L_10.13, R91.1
unnamed: L4.2, L_10.14, R90.1
unnamed: L_1.8, L_2.8, L_5.6, M_1.8, M_2.8, N_1.8, N_2.8
unnamed: L_5.1, P_8.15
unnamed: L_5.4, M_5.2
unnamed: L_5.10, P_8.5
unnamed: L_8.1, Q4.2
unnamed: L_8.2, Q4.1, R56.2
unnamed: L_8.6, L_8.7
unnamed: L_8.8, L_8.9
unnamed: L_8.13, Q5.1, R65.2
unnamed: L_8.14, Q5.2
unnamed: L_9.7, Q5.3, R61.1
unnamed: M_4.8, M_5.6, R_4.8
unnamed: M_5.3, N_4.8, P_4.8
unnamed: M_6.1, M_7.7
unnamed: M_6.3, M_7.10
unnamed: M_6.8, M_7.2
unnamed: M_6.10, M_7.15
unnamed: M_7.9, N_6.8
unnamed: M_8.7, Q4.3, R57.1
unnamed: M_9.5, M_9.6, N_9.10, R60.2
unnamed: M_9.12, M_9.13, N_9.4, R59.2
unnamed: M_10.6, N_9.1
unnamed: N_5.1, N_5.2, P_5.3
unnamed: N_5.6, P_5.5
unnamed: N_5.8, N_6.9
unnamed: N_6.11, P_8.6
unnamed: N_7.2, N_8.4
unnamed: N_7.5, R48.2
unnamed: N_7.7, R47.2
unnamed: N_7.10, R46.2
unnamed: N_7.12, R45.2
unnamed: N_7.14, N_7.15
unnamed: N_8.7, R51.1
unnamed: N_9.6, N_9.9, R132.1, R133.2
unnamed: N_9.8, Q15.2, R134.2
unnamed: N_10.8, R68.2
unnamed: N_9.12, N_10.13, R85.2
unnamed: N_11.2, R105.1
unnamed: N_11.5, R106.2
unnamed: N_11.7, R107.2
unnamed: N_11.10, R108.2
unnamed: N_11.15, R109.1
unnamed: P_5.1, P_9.12
unnamed: P_5.2, R_9.12
unnamed: P_6.3, R19.2, R_6.16
unnamed: P_6.4, R21.2, R_6.14
unnamed: P_6.5, R23.2, R_6.12
unnamed: P_6.6, R26.2, R_6.10
unnamed: P_6.10, R25.2, R_6.9
unnamed: P_6.11, R24.2, R_6.11
unnamed: P_6.12, R22.2, R_6.13
unnamed: P_6.13, R20.2, R_6.15
unnamed: P_9.1, P_9.2, R_9.13
unnamed: P_11.9, R77.1, R78.1, R81.1, R82.1, R83.1, R84.1, R86.2, R102.1
unnamed: P_11.13, R110.2, R111.1
unnamed: Q1.1, R52.2
unnamed: Q2.1, R50.2
unnamed: Q3.1, R54.2
unnamed: Q6.1, R64.2
unnamed: Q7.2, R34.1, R35.1, R36.1, R37.1, R38.1, R39.2
unnamed: Q11.1, R108.1
unnamed: Q12.1, R106.1
unnamed: Q13.1, R107.1
unnamed: Q14.2, R133.1
unnamed: Q16.2, R141.2, R146.1
unnamed: Q17.2, R143.1, R144.2
unnamed: R40.2, R_7.3
unnamed: R41.2, R_7.6
unnamed: R42.2, R_7.8
unnamed: R43.2, R_7.11
unnamed: R67.2, R68.1, R69.1, R_10.7
unnamed: R75.2, R_11.8
unnamed: R_7.2, R_7.5, R_7.10, R_7.13, R_8.9
unnamed: T10.1, T11.1
unnamed: T12.1, T13.1
unnamed: T14.1, T15.1
unnamed: T16.1, T17.1
O2: B_2.3, B_6.9, E_5.10, TP2.1, TP2.2
O_2: B_2.17, C_3.39, J21.31
PLAYER_1_: J20.J, Q14.3
PLAYER_2_: J20.7, Q15.3
PR27: F_5.4, F_8.12, F_10.1, H_5.4, J_5.4, K_5.11, K_7.1, K_8.12, M_7.1, P_8.1, P_8.7, P_8.10, R27.1, R_8.10, R_8.13
PR29: A_7.1, A_7.4, A_7.13, A_9.5, B_7.1, B_7.6, C_3.2, C_3.4, C_3.38, C_4.1, C_4.3, C_4.4, C_4.5, C_4.6, C_4.7, C_4.9, C_4.10, C_5.5, C_5.7, C_7.1, D_4.4, D_4.13, D_7.1, D_7.3, K_3.6, K_3.10, R29.1
R1: C116.1, J20.F, M_12.2, Q13.2
R/~WB: B_2.18, C_6.9, D_2.10, D_6.6, E_2.10, E_3.1, K_3.5, P_2.11, R_2.1
RAMSEL: N_5.4, N_9.5, N_11.12
ROT_LEFT_: C78.2, J20.15, J_10.12, R92.1
ROT_RIGHT_: C76.2, J20.S, J_10.13, R94.1
RST_: A_9.11, C_3.40, C_5.1, D_4.8, D_8.1, E_6.9, J20.W, K_6.2, K_9.9, M_10.15, N_7.1, N_11.1, P_7.1
R_COIN_SW_: C80.2, J20.R, L12.1
R_W: B_2.2, C_3.34, J21.32, TP3.1, TP3.2
SAUCRFIREEN: M_8.4, M_10.5, N_9.11
SAUCRFIRESND: CR6.2, R58.2, R81.2
SAUCRSND: P_10.4, R77.2
SAUCRSNDEN: M_10.4, N_9.13
SCALE0: K_7.15, M_7.13, R38.2
SCALE1: K_7.6, M_7.4, R37.2
SCALE2: K_7.12, M_7.12, R36.2
SCALE3: K_7.9, M_7.5, R35.2
SELF_TEST_: C74.2, J20.L, L2.1
SHCON: B_12.5, B_12.6, C89.2, D_12.5, D_12.6, Q10.3, R115.1
SHPFIREEN: L_9.4, M_10.9, N_9.3
SHPFIRESND: CR8.2, R66.2, R84.2
SHPSND: C69.1, P_11.1, R102.2, R103.1
SHPTHRUSTEN: M_10.7, R80.2, R_11.6
SLAM_: C83.2, J20.9, L3.1
STRT_1_LED_: J20.8, R105.2
STRT_1_SW_: C77.2, J20.N, L8.1
STRT_2_LED_: J20.6, R109.2
STRT_2_SW_: C75.2, J20.P, L6.1
THRUST_: C79.2, J20.14, J_10.14, R99.1
THUMPSND: R74.2, R83.2
TIMER0: A_9.13, A_9.14, B_5.3, B_9.13, D_4.1, E_5.5, E_6.12, F_6.13, F_7.15, H_6.1, H_6.15, J_6.1, J_6.15, K_5.5
TIMER1: E_5.1, E_6.2, F_6.3, F_7.6, N_5.10
TIMER2: E_5.2, E_6.5, F_6.10, F_7.12
TIMER3: E_5.4, E_6.1, E_6.4, E_6.13, F_6.6, F_7.9, N_5.9
UNMDACX1: C_10.11, E_9.3
UNMDACX2: C_10.5, E_9.2
UNMDACX3: C_10.14, E_9.6
UNMDACX4: C_10.2, E_9.7
UNMDACX5: DE_10.11, D_9.3
UNMDACX6: DE_10.5, D_9.2
UNMDACX7: DE_10.14, D_9.6
UNMDACX8: DE_10.2, D_9.7
UNMDACX9: C_9.3, E_10.14
UNMDACX10: C_9.2, E_10.2
UNMDACX11: C_9.6, C_10.1, DE_10.1, E_10.1
UNMDACY1: A_10.11, J_9.3
UNMDACY2: A_10.5, J_9.2
UNMDACY3: A_10.14, J_9.6
UNMDACY4: A_10.2, J_9.7
UNMDACY5: BC_10.11, H_9.3
UNMDACY6: BC_10.5, H_9.2
UNMDACY7: BC_10.14, H_9.6
UNMDACY8: BC_10.2, H_9.7
UNMDACY9: FH_10.11, F_9.3
UNMDACY10: FH_10.14, F_9.2
UNMDACY11: A_10.1, BC_10.1, FH_10.1, F_9.6
VGCK: A_7.2, A_7.11, B_2.5, B_7.2, B_9.4, C_7.2, D_7.2, F_8.9, H_8.9, J_8.9, K_8.9
WRA: F_4.5, F_4.14, H_4.5, H_4.14, J_4.5, J_4.14, K_5.3
WRB: F_4.4, F_4.13, H_4.4, H_4.13, J_4.4, J_4.13, K_5.2
XVLD: E_10.7, F_10.11
XVLD*: B_8.9, F_10.10
X_OUT_: C102.2, C_12.1, J20.17, R120.1, R120.2, TP50.1, TP50.2
YVLD: FH_10.4, F_10.3
YVLD*: B_8.10, F_10.2
Y_DAC: A_12.6, B_11.2, B_11.15, B_11A1.18, C105.2
Y_OUT_: A_12.1, C110.2, J20.18, R126.1, R126.2, TP60.1, TP60.2
Z_OUT_: J20.M, Q9.1, R72.1, TP70.1, TP70.2
~ALPHANUM: B_9.1, E_5.6, F_6.1, J_7.1, K_6.5
~AUDIO: L_6.7, M_10.14
~BLANK: D_6.13, K_9.1
~BUFFEN: K_3.9, P_2.9, R_2.19
~DMACNT: B_8.12, L_6.5
~DMAGO: B_8.13, K_6.1, L_6.1
~DMALD: B_9.9, D_4.2, E_8.2, F_5.11, H_5.11, J_5.11
~DMAPUSH: B_5.1, E_8.1, K_6.10
~EXPLODE: L_6.4, P_7.9
~GO: A_9.7, B_8.2, E_9.4, J_9.4
~GO*: F_8.10, F_8.11, F_8.13, H_8.13, H_10.2, J_8.13, K_8.10, K_8.11, K_8.13
~GOSTROBE: B_6.1, E_8.3
~HALT: A_9.1, A_9.9, B_8.1
~HALTSTROBE: A_9.12, B_9.12, E_8.4
~LATCH0: B_8.5, B_9.2, E_8.5, H_7.11
~LATCH1: E_8.6, F_7.11
~LATCH2: B_8.4, E_8.7, J_7.11, N_6.10
~LATCH3: E_8.9, K_6.13
~LDSTROBE: B_9.11, C_9.11, D_9.11, E_9.11, F_9.11, H_9.11, J_9.11
~NOISERESET: L_6.9, P_9.9, R_9.9
~O2: B_6.8, K_3.11, M_5.10, M_5.12
~OPTS: E_4.6, P_6.1, P_6.15
~OUT: L_6.2, N_11.9
~PMEM: E_4.9, L_3.1
~PROM0: F_1.20, F_2.10, H_1.10, L_1.10, L_2.10, L_3.5
~PROM1: DE_1.20, H_2.10, J_1.10, L_3.6, M_1.10, M_2.10
~PROM2: C_1.20, J_2.10, K_1.10, L_3.7, N_1.10, N_2.10
~SAUCRSEL: N_9.2, N_10.5, N_10.6, R63.2
~SINP0: E_4.4, L_10.7
~SINP1: E_4.5, J_10.7
~STOP: A_8.12, A_9.3
~TEST: C_5.10, L2.2, L_10.12, R87.1
~THUMP: L_6.6, N_7.9
~UNMDACX12: C_10.3, C_10.6, C_10.10, C_10.13, DE_10.3, DE_10.6, DE_10.10, DE_10.13, E_10.3, E_10.5, E_10.13, H_10.12
~UNMDACY12: A_10.3, A_10.6, A_10.10, A_10.13, BC_10.3, BC_10.6, BC_10.10, BC_10.13, FH_10.2, FH_10.10, FH_10.13, H_10.10
~VGCK*: A_7.6, C_6.12
~VMEM: A_7.12, E_4.10, F_3.1, H_3.1, J_3.1, K_3.1
~VRAM: L_3.12, M_5.1, M_5.4, TP30.1, TP30.2
~VROM1: L_3.11, PD11.1, R_3.20
~VROM2: K_4.10, L_3.10, L_4.10, NP_3.20, PD10.1, PD10.2, PD11.2
~VW: M_4.10, M_5.8, N_4.10, P_4.10, R_4.10
~WDCLR: C_6.4, L_6.3
~ZPAGE: E_4.12, M_5.13

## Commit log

2019-12-17 Transferred prooject into github
2021-01-08 Moved the IC silkscreen identifiers to areas they can be seen after soldering
2021-01-08 Changed the silkscreen on the components so the compinent IDs can be seen after soldering
2021-01-08 Updated the BOM
2021-01-09 Added the ROM adapter design files and updated the readme file
2021-01-09 Fixed typos
